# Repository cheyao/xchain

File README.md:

# XOR keychain

Ever wondered how a xor worked? With this keychain you can have a open XOR circuit on your keychain! Made with only transistors and resistors, learn how it works!

## Schematic

## PCB

Check out https://solder.hackclub.com/ to build a PCB, and get it made for free!

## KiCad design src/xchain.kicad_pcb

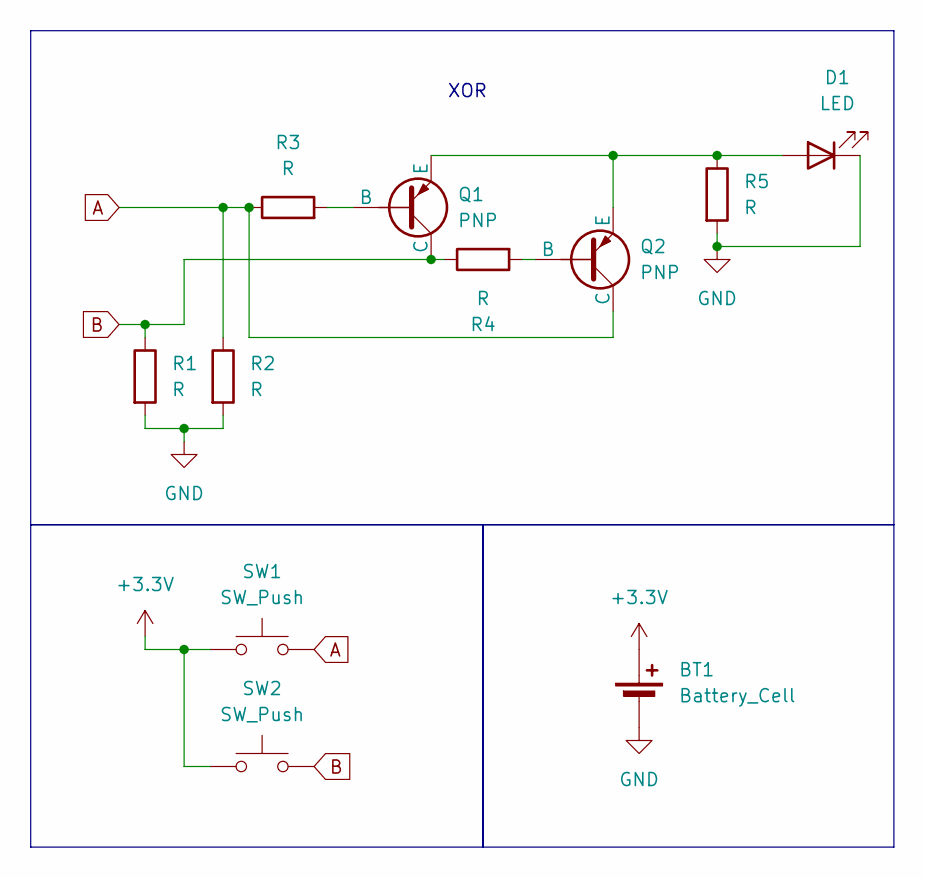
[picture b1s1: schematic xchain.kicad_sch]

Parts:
BT1: Battery_Cell; BatteryHolder_Keystone_3034_1x20mm
D1: LED; LED_D5.0mm
Q1, Q2: PNP; TO-92L_HandSolder
R1, R2, R3, R4, R5: R; R_Axial_DIN0207_L6.3mm_D2.5mm_P7.62mm_Horizontal
SW1, SW2: SW_Push; SW_PUSH_6mm

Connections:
+3.3V: BT1.1 (+), SW1.1, SW2.1
A: Q2.1 (C), R2.1, R3.1, SW1.2
B: Q1.1 (C), R1.1, R4.1, SW2.2
GND: BT1.2 (-), D1.1 (K), R1.2, R2.2, R5.2
unnamed: D1.2 (A), Q1.3 (E), Q2.3 (E), R5.1
unnamed: Q1.2 (B), R3.2
unnamed: Q2.2 (B), R4.2

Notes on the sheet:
XOR

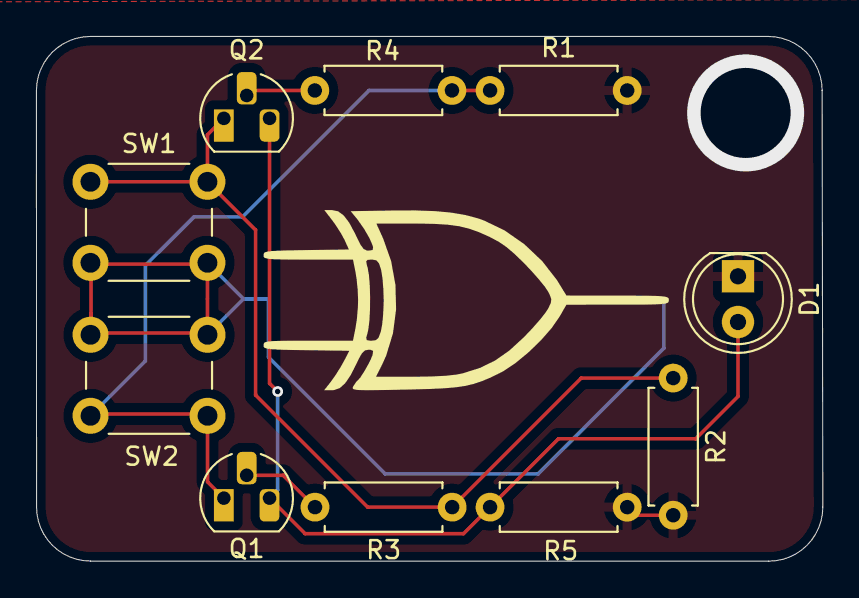
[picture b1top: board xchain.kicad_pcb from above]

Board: 2 copper layers, 43.7 x 29.2 mm, 11 parts (1 on the bottom side), 7 nets.

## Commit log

2025-03-28 Push v1
2025-04-03 Revision
